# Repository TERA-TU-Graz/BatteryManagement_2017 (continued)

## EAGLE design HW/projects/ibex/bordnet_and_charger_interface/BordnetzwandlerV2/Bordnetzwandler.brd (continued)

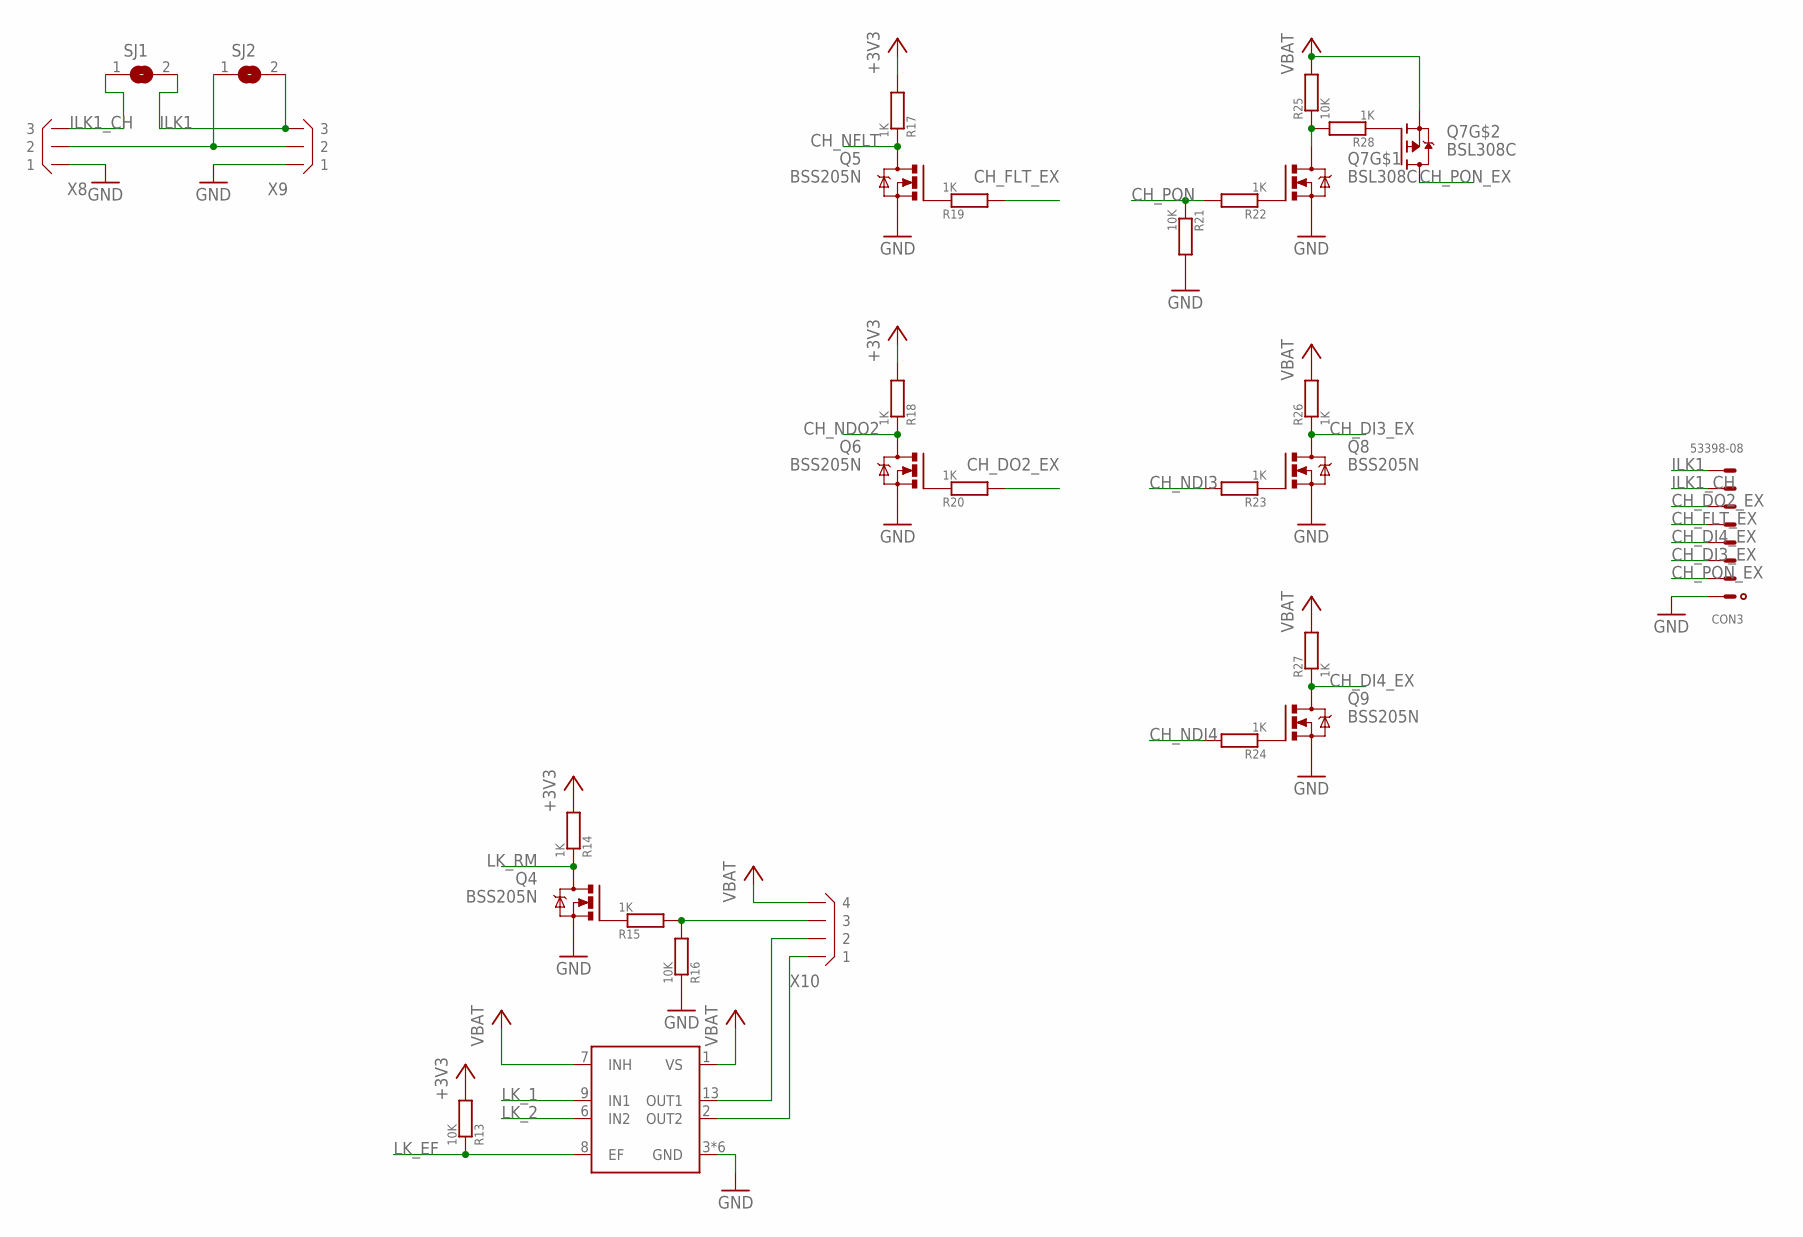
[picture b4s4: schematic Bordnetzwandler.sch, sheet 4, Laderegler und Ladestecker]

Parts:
CON3: 53398-08
IC5: TLE4207GN; INF-PG-DSO-14-22_N_1PRIMARY
Q4, Q5, Q6, Q8, Q9: BSS205N; SOT23
Q7: BSL308C; TSOP-6
R13, R16: 10K; R0805
R14, R15: 1K; R0805
R17, R18, R19, R20, R22, R23, R24, R26, R27, R28: 1K; R0603
R21, R25: 10K; R0603
SJ1, SJ2: SJ
X8, X9: B3B-XH
X10: B4B-XH

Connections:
+3V3: R13.2, R14.2, R17.2, R18.2; also elsewhere on the board
CH_DI3_EX: CON3.3, Q8.3 (D), R26.1
CH_DI4_EX: CON3.4, Q9.3 (D), R27.1
CH_DO2_EX: CON3.6, R20.2
CH_FLT_EX: CON3.5, R19.2
CH_NDI3: R23.2; also elsewhere on the board
CH_NDI4: R24.2; also elsewhere on the board
CH_NDO2: Q6.3 (D), R18.1; also elsewhere on the board
CH_NFLT: Q5.3 (D), R17.1; also elsewhere on the board
CH_PON: R21.1, R22.2; also elsewhere on the board
CH_PON_EX: CON3.2, Q7.P$4 (D)
GND: CON3.1, IC5.3 (GND), IC5.4 (GND), IC5.5 (GND), IC5.10 (GND), IC5.11 (GND), IC5.12 (GND), Q4.2 (S), Q5.2 (S), Q6.2 (S), Q7.P$5 (S), Q8.2 (S), Q9.2 (S), R16.1, R21.2, X8.P$1 (1), X9.P$1 (1); also elsewhere on the board
ILK1: CON3.8, SJ1.2, SJ2.2, X9.P$3 (3)
ILK1_CH: CON3.7, SJ1.1, X8.P$3 (3)
ILK2: SJ2.1, X8.P$2 (2), X9.P$2 (2)
LK_1: IC5.9 (IN1); also elsewhere on the board
LK_2: IC5.6 (IN2); also elsewhere on the board
LK_EF: IC5.8 (EF), R13.1; also elsewhere on the board
LK_RM: Q4.3 (D), R14.1; also elsewhere on the board
unnamed: Q6.1 (G), R20.1
unnamed: Q8.1 (G), R23.1
unnamed: Q4.1 (G), R15.1
unnamed: R15.2, R16.2, X10.P$3 (3)
unnamed: Q7.P$3 (G), R28.1
unnamed: IC5.13 (OUT1), X10.P$2 (2)
unnamed: IC5.2 (OUT2), X10.P$1 (1)
unnamed: Q7.P$1 (G), R22.1
unnamed: Q9.1 (G), R24.1
unnamed: Q5.1 (G), R19.1
unnamed: Q7.P$6 (D), R25.1, R28.2
VBAT: IC5.1 (VS), IC5.7 (INH), Q7.P$2 (S), R25.2, R26.2, R27.2, X10.P$4 (4); also elsewhere on the board

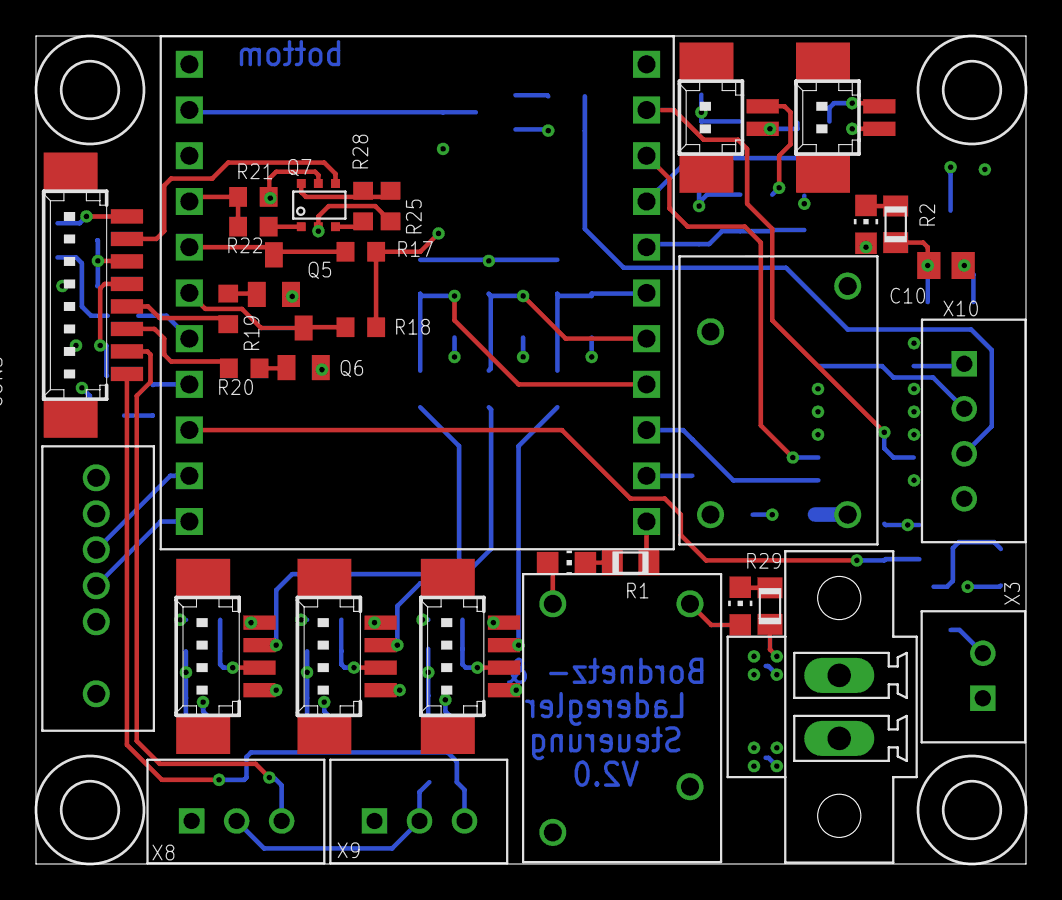
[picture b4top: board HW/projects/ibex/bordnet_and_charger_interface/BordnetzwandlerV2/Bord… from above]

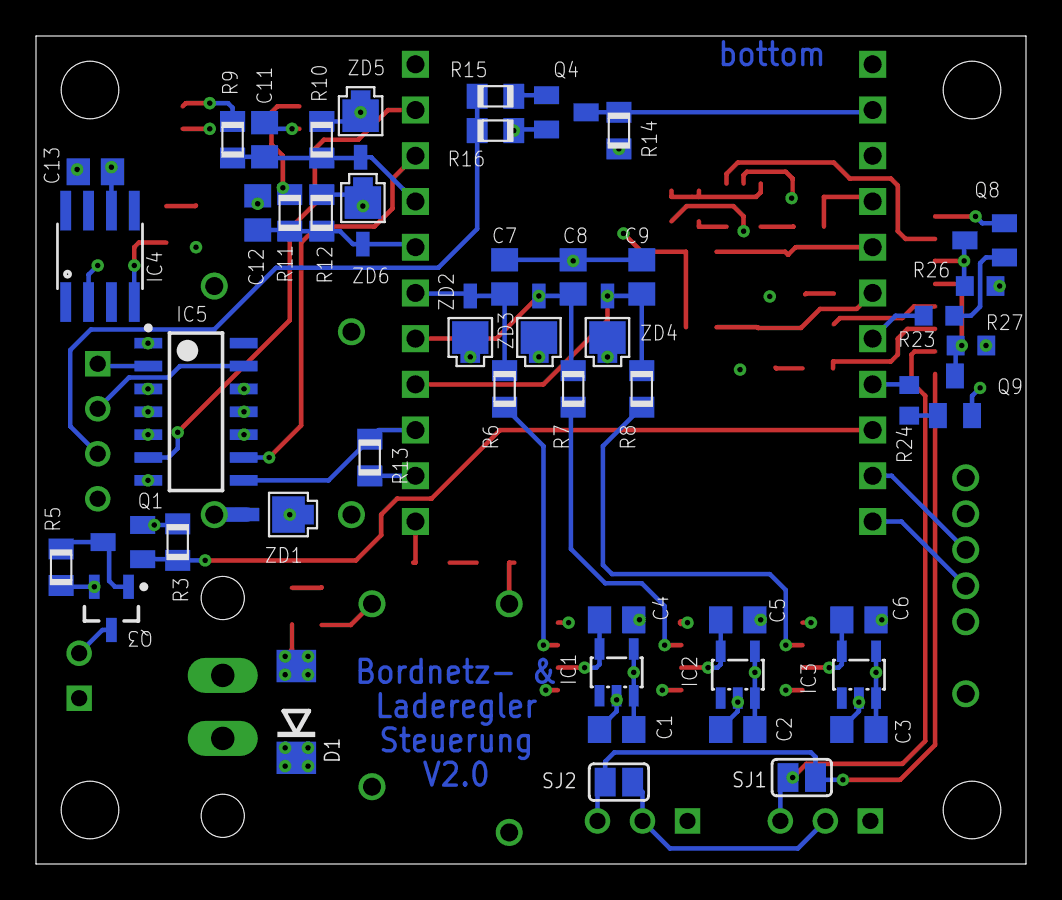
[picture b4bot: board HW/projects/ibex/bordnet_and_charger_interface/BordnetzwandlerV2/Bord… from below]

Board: 4 copper layers, 55.0 x 46.0 mm, 85 parts (48 on the bottom side), 54 nets.
